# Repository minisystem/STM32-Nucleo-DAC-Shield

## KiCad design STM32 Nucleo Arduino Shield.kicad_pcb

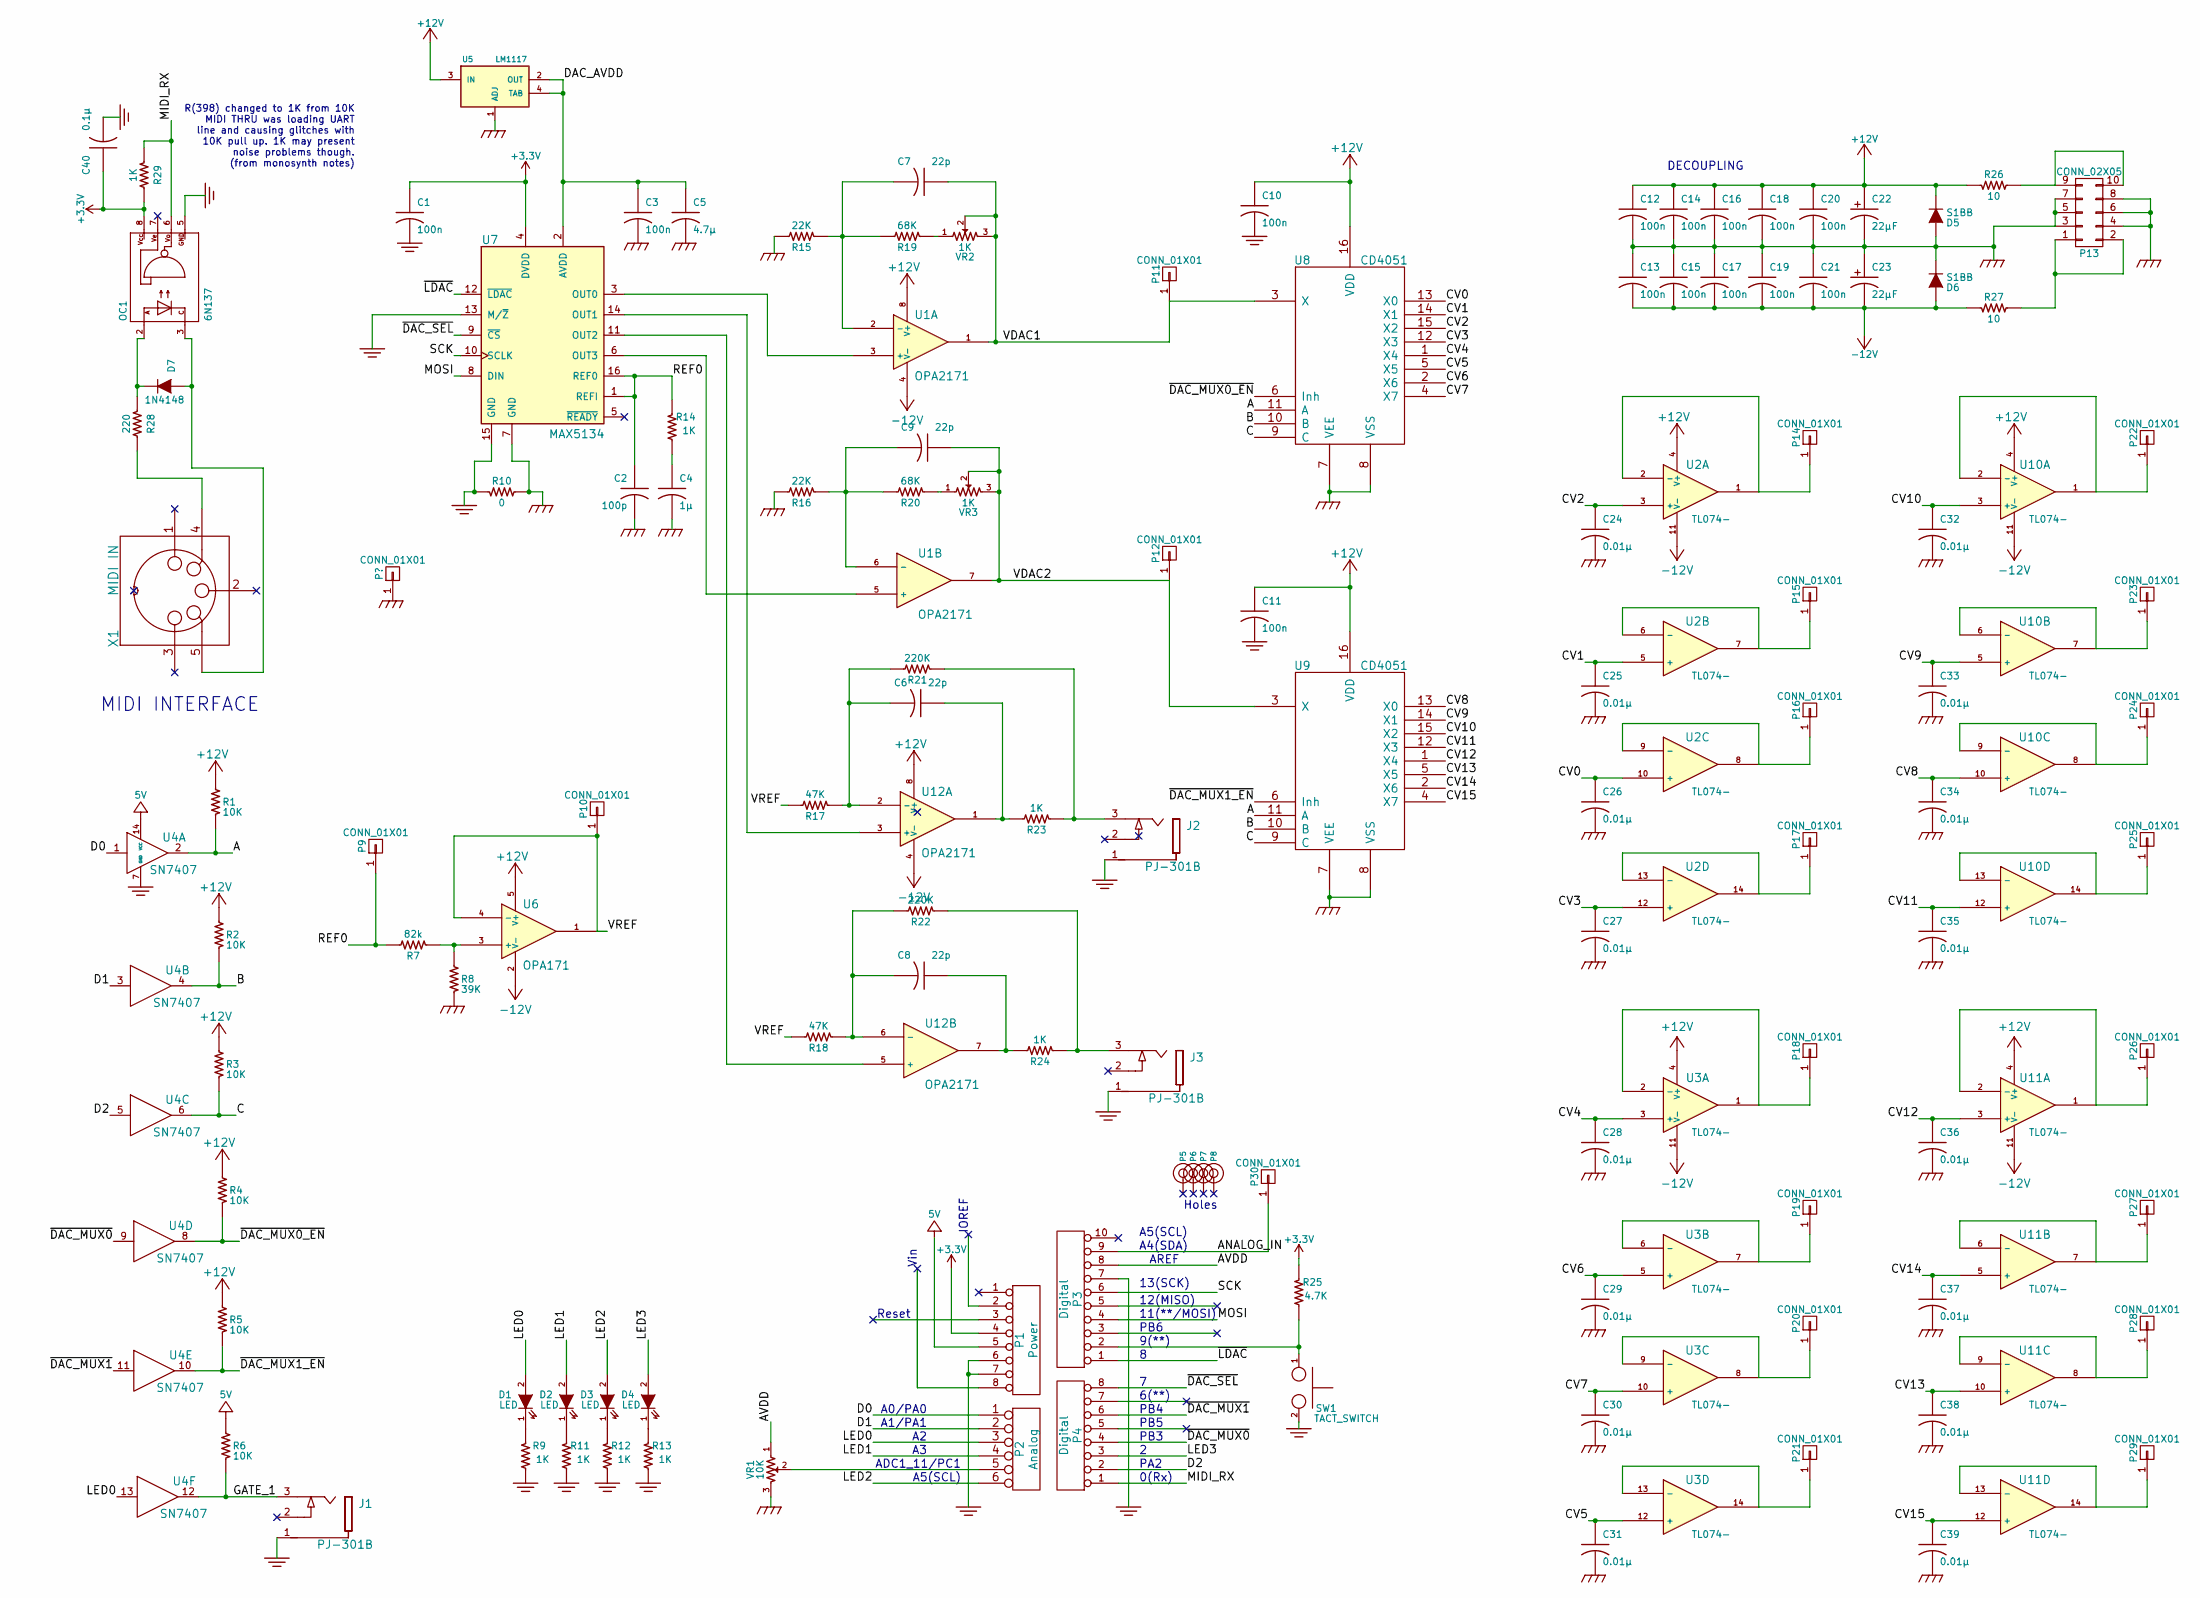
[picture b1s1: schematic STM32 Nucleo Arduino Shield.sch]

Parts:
C1, C3, C10, C11, C12, C13, C14, C15, C16, C17, C18, C19, C20, C21: 100n; SM0603-C-JRL
C2: 100p; SM0603-C-JRL
C4: 1μ; SM0603-C-JRL
C5: 4.7μ; SM0805-HAND
C6, C7, C8, C9: 22p; SM0603-C-JRL
C22, C23: 22μF; jrl_c_elec_5x5.3; Part Number UWJ1E100MCL1GB
C24, C25, C26, C27, C28, C29, C30, C31, C32, C33, C34, C35, C36, C37, C38, C39: 0.01µ; SM0603-C-JRL
C40: 0.1µ; SM0603-C-JRL
D1, D2, D3, D4: LED; LED-0805-JRL
D5, D6: S1BB; SMB-1C2A
D7: 1N4148; SOD323-C1A2
J1, J2, J3: PJ-301B; PJ-301B-JACK-SLOTS
OC1: 6N137; 8-SMD
P1: Power; Socket_Strip_Arduino_1x08
P2: Analog; Socket_Strip_Arduino_1x06
P3: Digital; Socket_Strip_Arduino_1x10
P4: Digital; Socket_Strip_Arduino_1x08
P5, P6, P7, P8: CONN_1; Arduino_1pin
P9, P10, P11, P12, P14, P15, P16, P17, P18, P19, P20, P21, P22, P23, P24, P25, P26, P27, P28, P29, P30: CONN_01X01; TEST_POINT_SMALL
P13: CONN_02X05; Pin_Header_Straight_2x05_Pitch2.54mm
R1, R2, R3, R4, R5, R6: 10K; SM0603-R-JRL
R7: 82k; SM0603-R-JRL
R8: 39K; SM0603-R-JRL
R9, R11, R12, R13, R14, R23, R24, R29: 1K; SM0603-R-JRL
R10: 0; SM0603-R-JRL
R15, R16: 22K; SM0603-R-JRL
R17, R18: 47K; SM0603-R-JRL
R19, R20: 68K; SM0603-R-JRL
R21, R22: 220K; SM0603-R-JRL
R25: 4.7K; SM0603-R-JRL
R26, R27: 10; SM0805-HAND
R28: 220; SM0603-R-JRL
SW1: TACT_SWITCH; B3F-1050-OMRON
U1, U12: OPA2171; TSSOP-8_3x3mm_Pitch0.65mm
U2, U3, U10, U11: TL074-; TSSOP-14_4.4x5mm_Pitch0.65mm
U4: SN7407; SOIC-14_3.9x8.7mm_Pitch1.27mm
U5: LM1117; SOT-223
U6: OPA171; SOT-23-5
U7: MAX5134; TSSOP-16_4.4x5mm_Pitch0.65mm
U8, U9: CD4051; TSSOP-16_4.4x5mm_Pitch0.65mm_jrl
VR1: 10K; R0904N-SONG-HUEI
VR2, VR3: 1K; TC33X-2
X1: MIDI IN; SD-50BV-5DIN

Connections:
+3V3: C1.1, C40.1, OC1.8, P1.4, R25.1, R29.2, U7.4 (DVDD)
+5V: P1.5, R6.2, U4.14 (VCC)
+12V: C10.1, C11.1, C12.1, C14.1, C16.1, C18.1, C20.1, C22.1 (+), D5.1 (K), R1.2, R2.2, R3.2, R4.2, R5.2, R26.1, U1.8 (V+), U2.4 (V+), U3.4 (V+), U5.3 (IN), U6.5 (V+), U8.16 (VDD), U9.16 (VDD), U10.4 (V+), U11.4 (V+), U12.8 (V+)
-12V: C13.2, C15.2, C17.2, C19.2, C21.2, C23.2 (-), D6.2 (A), R27.1, U1.4 (V-), U2.11 (V-), U3.11 (V-), U6.2 (V-), U10.11 (V-), U11.11 (V-), U12.4 (V-)
/A: R1.1, U4.2, U8.11 (A), U9.11 (A)
/ANALOG_IN: P3.9, P30.1
/AVDD: P3.8, VR1.1
/B: R2.1, U4.4, U8.10 (B), U9.10 (B)
/C: R3.1, U4.6, U8.9 (C), U9.9 (C)
/CV0: C26.1, U2.10 (+), U8.13 (X0)
/CV1: C25.1, U2.5 (+), U8.14 (X1)
/CV2: C24.1, U2.3 (+), U8.15 (X2)
/CV3: C27.1, U2.12 (+), U8.12 (X3)
/CV4: C28.1, U3.3 (+), U8.1 (X4)
/CV5: C31.1, U3.12 (+), U8.5 (X5)
/CV6: C29.1, U3.5 (+), U8.2 (X6)
/CV7: C30.1, U3.10 (+), U8.4 (X7)
/CV8: C34.1, U9.13 (X0), U10.10 (+)
/CV9: C33.1, U9.14 (X1), U10.5 (+)
/CV10: C32.1, U9.15 (X2), U10.3 (+)
/CV11: C35.1, U9.12 (X3), U10.12 (+)
/CV12: C36.1, U9.1 (X4), U11.3 (+)
/CV13: C38.1, U9.5 (X5), U11.10 (+)
/CV14: C37.1, U9.2 (X6), U11.5 (+)
/CV15: C39.1, U9.4 (X7), U11.12 (+)
/D0: P2.1, U4.1
/D1: P2.2, U4.3
/D2: P4.2, U4.5
/DAC_AVDD: C3.1, C5.1, U5.2 (OUT), U5.4 (TAB), U7.2 (AVDD)
/GATE_1: J1.3, R6.1, U4.12
/LED0: D1.2 (A), P2.3, U4.13
/LED1: D2.2 (A), P2.4
/LED2: D3.2 (A), P2.6
/LED3: D4.2 (A), P4.3
/MIDI_RX: OC1.6, P4.1, R29.1
/MOSI: P3.4, U7.8 (DIN)
/REF0: C2.1, P9.1, R7.2, R14.1, U7.1 (REFI), U7.16 (REF0)
/SCK: P3.6, U7.10 (SCLK)
/VDAC1: C7.1, P11.1, U1.1, U8.3 (X), VR2.2, VR2.3
/VDAC2: C9.1, P12.1, U1.7, U9.3 (X), VR3.2, VR3.3
/VREF: P10.1, R17.2, R18.2, U6.1, U6.4 (-)
/~DAC_MUX0: P4.4, U4.9
/~DAC_MUX0_EN: R4.1, U4.8, U8.6 (Inh)
/~DAC_MUX1: P4.6, U4.11
/~DAC_MUX1_EN: R5.1, U4.10, U9.6 (Inh)
/~DAC_SEL: P4.8, U7.9 (~CS~)
/~LDAC: P3.1, U7.12 (~LDAC~)
unnamed: C4.1, R14.2
unnamed: C6.1, R23.2, U12.1
unnamed: C6.2, R17.1, R21.2, U12.2 (-)
unnamed: C7.2, R15.1, R19.2, U1.2 (-)
unnamed: C8.1, R24.2, U12.7
unnamed: C8.2, R18.1, R22.2, U12.6 (-)
unnamed: C9.2, R16.1, R20.2, U1.6 (-)
unnamed: D1.1 (K), R9.1
unnamed: D2.1 (K), R11.1
unnamed: D3.1 (K), R12.1
unnamed: D4.1 (K), R13.1
unnamed: D7.1 (K), OC1.2, R28.1
unnamed: D7.2 (A), OC1.3, X1.5
unnamed: J2.3, R21.1, R23.1
unnamed: J3.3, R22.1, R24.1
unnamed: P2.5, VR1.2
unnamed: P3.2, R25.2, SW1.1
unnamed: P13.1, P13.2, R27.2
unnamed: P13.9, P13.10, R26.2
unnamed: P14.1, U2.1, U2.2 (-)
unnamed: P15.1, U2.6 (-), U2.7
unnamed: P16.1, U2.8, U2.9 (-)
unnamed: P17.1, U2.13 (-), U2.14
unnamed: P18.1, U3.1, U3.2 (-)
unnamed: P19.1, U3.6 (-), U3.7
unnamed: P20.1, U3.8, U3.9 (-)
unnamed: P21.1, U3.13 (-), U3.14
unnamed: P22.1, U10.1, U10.2 (-)
unnamed: P23.1, U10.6 (-), U10.7
unnamed: P24.1, U10.8, U10.9 (-)
unnamed: P25.1, U10.13 (-), U10.14
unnamed: P26.1, U11.1, U11.2 (-)
unnamed: P27.1, U11.6 (-), U11.7
unnamed: P28.1, U11.8, U11.9 (-)
unnamed: P29.1, U11.13 (-), U11.14
unnamed: R7.1, R8.2, U6.3 (+)
unnamed: R19.1, VR2.1
unnamed: R20.1, VR3.1
unnamed: R28.2, X1.4
unnamed: U1.3 (+), U7.3 (OUT0)
unnamed: U1.5 (+), U7.6 (OUT3)
unnamed: U7.14 (OUT1), U12.3 (+)
unnamed: U7.11 (OUT2), U12.5 (+)

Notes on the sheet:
Reset
Vin
IOREF
A0/PA0
A1/PA1
ADC1_11/PC1
A5(SCL)
0(Rx)
PA2
PB3
PB5
PB4
6(**)
9(**)
PB6
AREF
A4(SDA)
Holes
13(SCK)
12(MISO)
11(**/MOSI)
MIDI INTERFACE
R(398) changed to 1K from 10K MIDI THRU was loading UART line and causing glitches with 10K pull up. 1K may present noise problems though. (from monosynth notes)
DECOUPLING

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
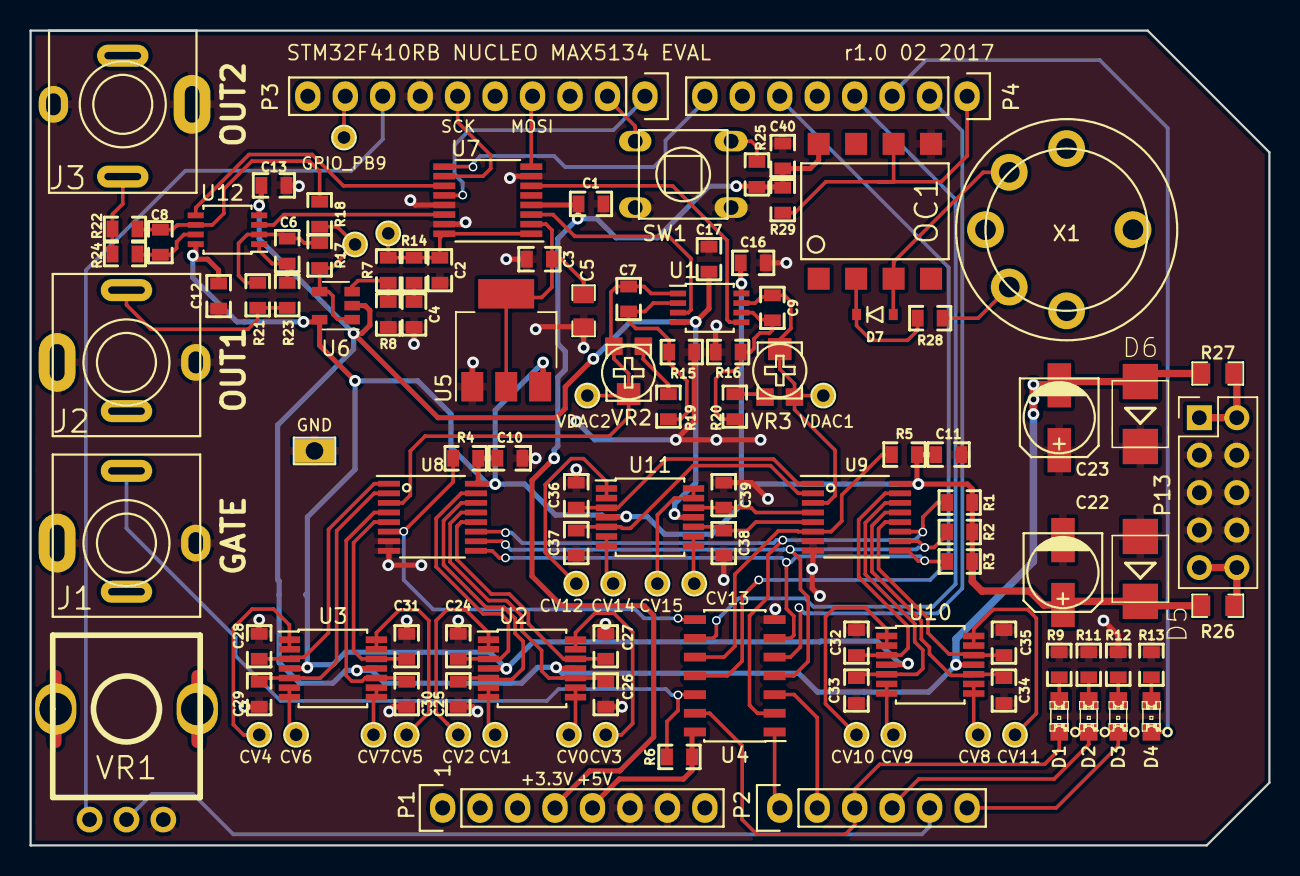
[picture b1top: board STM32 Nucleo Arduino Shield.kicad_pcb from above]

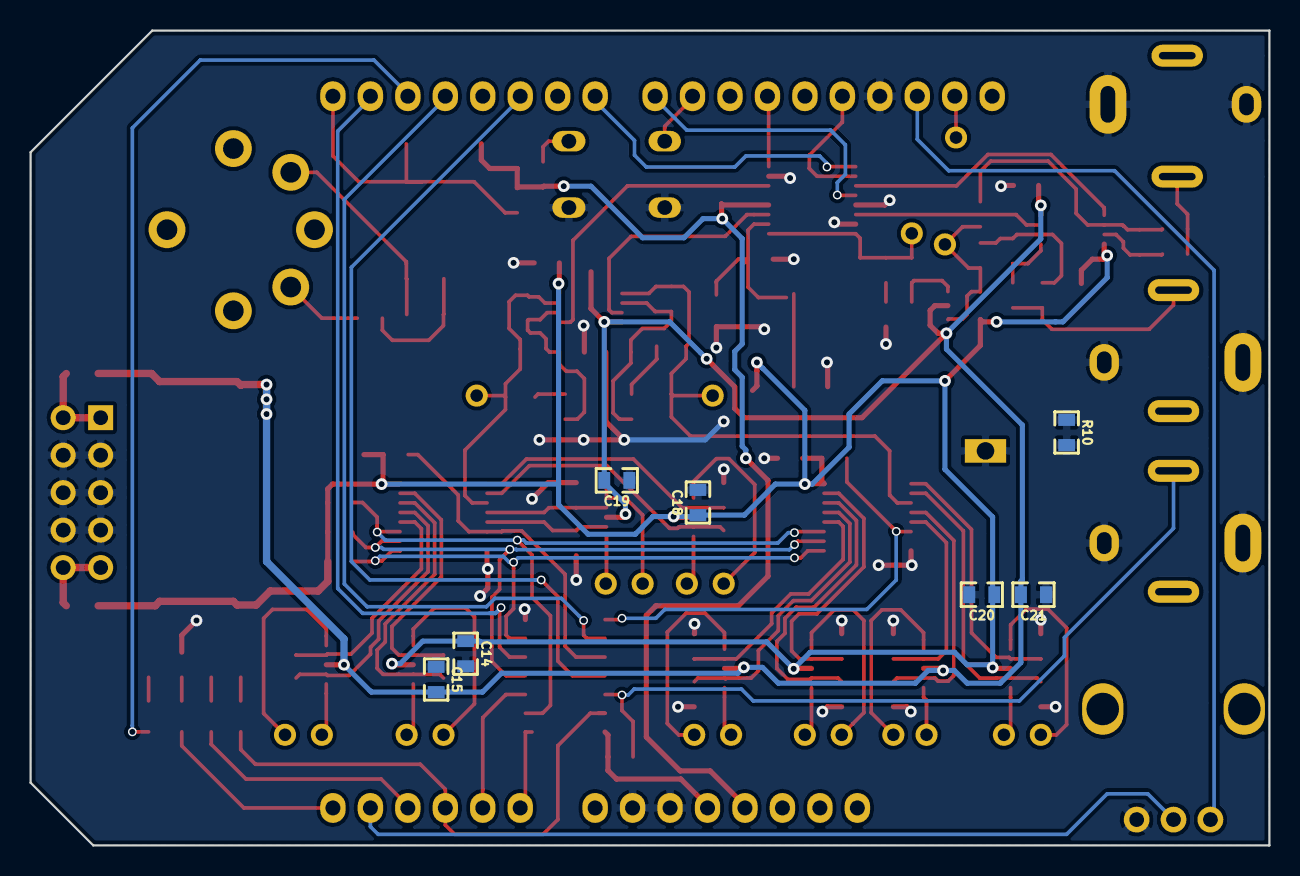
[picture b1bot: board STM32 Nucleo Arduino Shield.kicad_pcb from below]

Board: 2 copper layers, 84.0 x 55.2 mm, 124 parts (7 on the bottom side), 91 nets.

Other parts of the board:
P31: CONN_01X01; TEST_POINT_LOOP_4592

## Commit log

2017-01-30 adding a bunch of crap. as usual, evaluation board is getting out of hand
2017-01-31 footprints assigned, netlist generated, layout started
2017-02-01 routing routing routing
2017-02-02 more tedious routing
2017-02-03 mostly routed S&H circuits
2017-02-03 everything placed and routing. stitching ground
2017-02-03 routed. weird Socket_Arduino_Uno library glitch required reinstalling footprint library from Arduino tempalte folder
2017-02-03 ready for checking
2017-02-04 finished adding 3D models
2017-02-07 checked shield footprint and ordered PCBs
